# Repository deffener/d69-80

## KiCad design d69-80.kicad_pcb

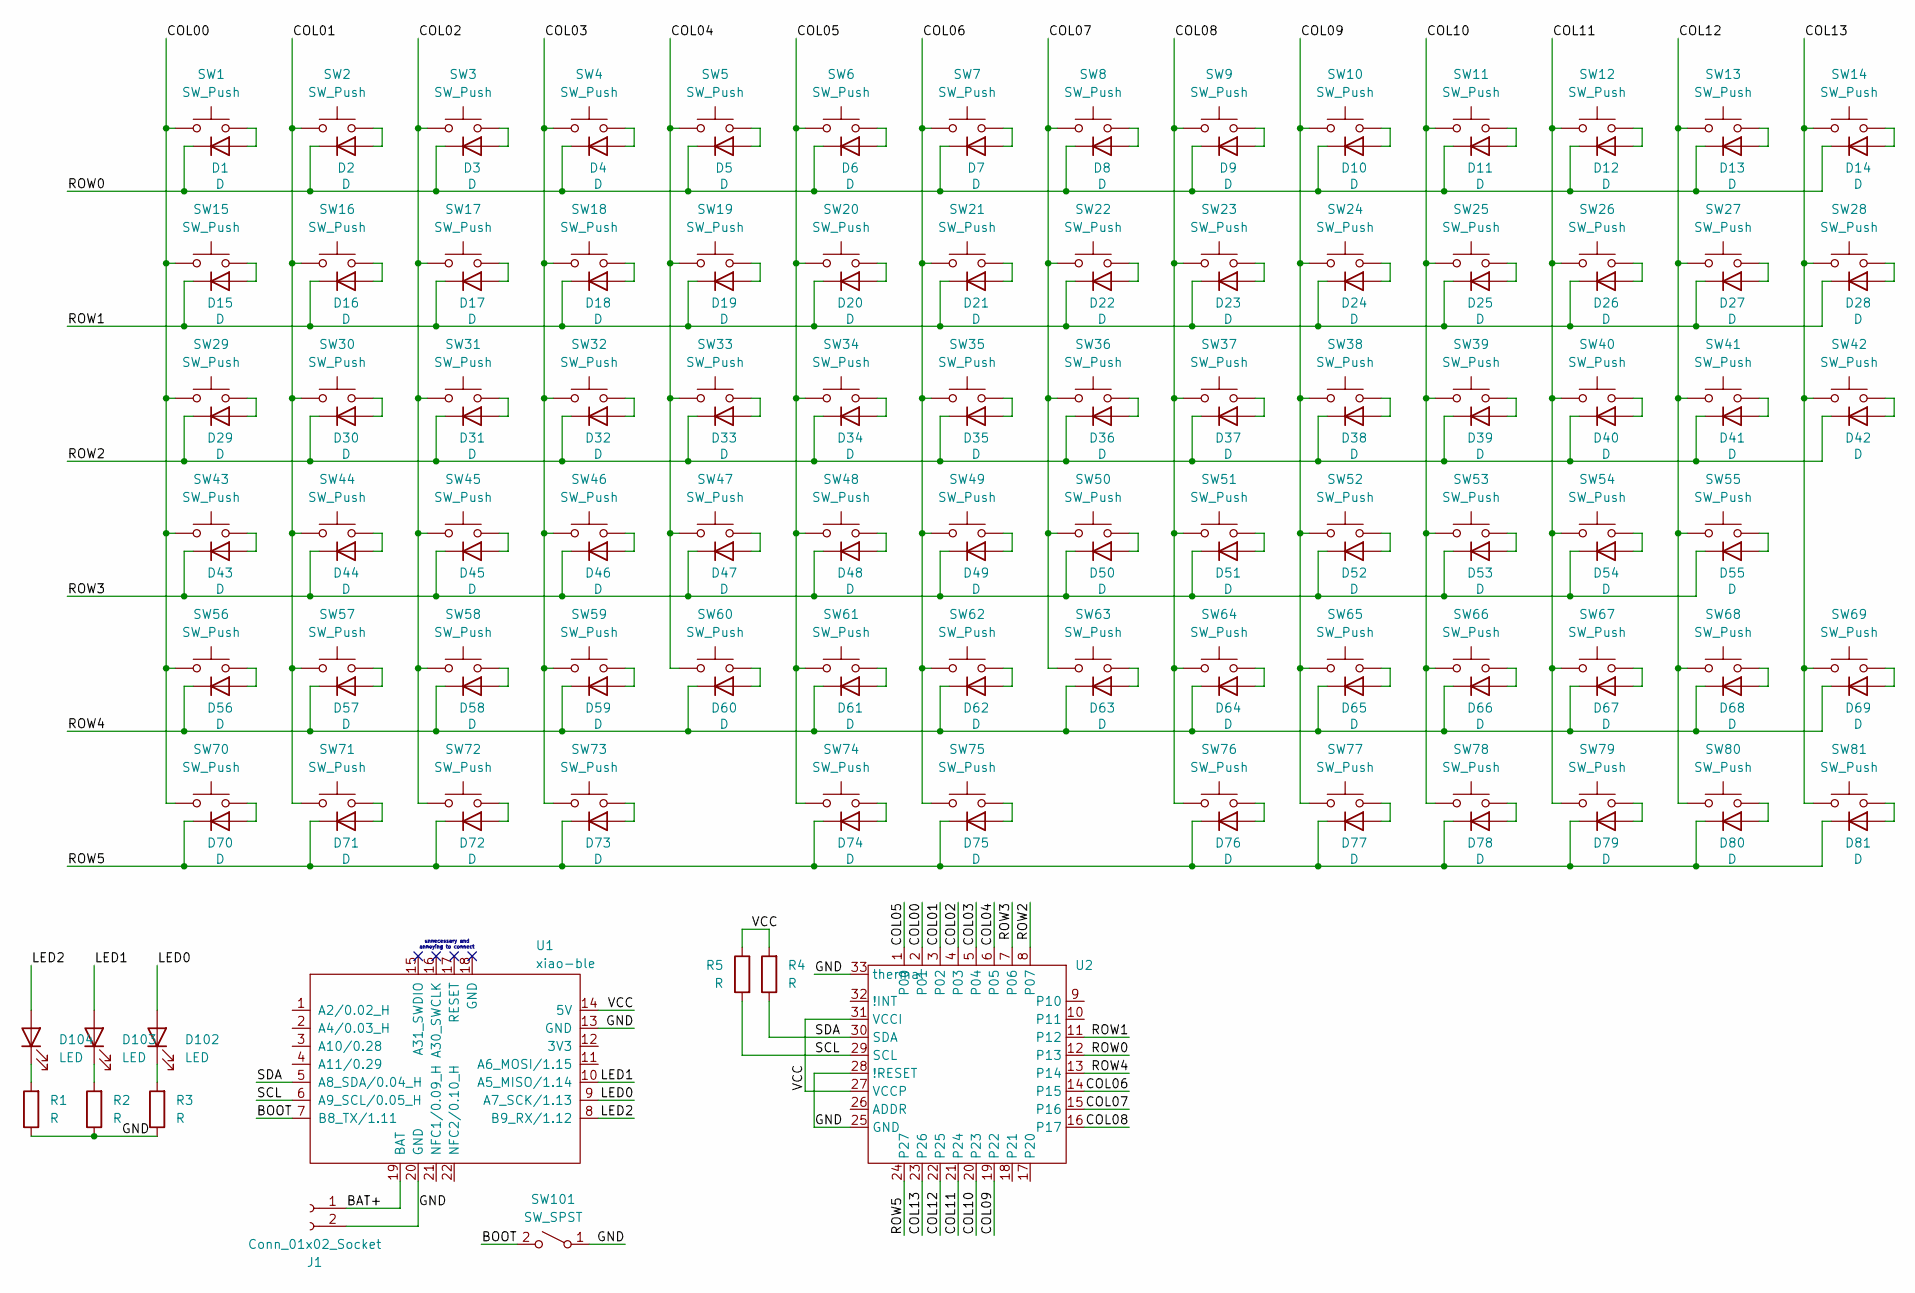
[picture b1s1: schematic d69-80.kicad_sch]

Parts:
D1, D2, D3, D4, D5, D6, D7, D8, D9, D10, D11, D12, D13, D14, D15, D16, D17, D18, D19, D20, D21, D22, D23, D24, D25, D26, D27, D28, D29, D30, D31, D32, D33, D34, D35, D36, D37, D38, D39, D40, D41, D42, D43, D44, D45, D46, D47, D48, D49, D50, D51, D52, D53, D54, D55, D56, D57, D58, D59, D60, D61, D62, D63, D64, D65, D66, D67, D68, D69, D70, D71, D72, D73, D74, D75, D76, D77, D78, D79, D80, D81: D; D_SOD-123
D102, D103, D104: LED; LED_0603_1608Metric_Pad1.05x0.95mm_HandSolder
J1: Conn_01x02_Socket; JST_XH_B2B-XH-AM_1x02_P2.50mm_Vertical
R1, R2, R3, R4, R5: R; R_0603_1608Metric_Pad0.98x0.95mm_HandSolder
SW1, SW15: SW_Push; SW_Hotswap_Kailh_Choc_V1_1.00u_mod3
SW2, SW3, SW4, SW5: SW_Push; SW_Hotswap_Kailh_Choc_V1_1.00u_mod2
SW6, SW7, SW8, SW9, SW10, SW11, SW12, SW13, SW14, SW16, SW17, SW18, SW19, SW20, SW21, SW22, SW23, SW24, SW25, SW26, SW27, SW30, SW31, SW32, SW33, SW34, SW35, SW36, SW37, SW38, SW39, SW40, SW41, SW44, SW45, SW46, SW47, SW48, SW49, SW50, SW51, SW52, SW53, SW54, SW55, SW56, SW57, SW58, SW59, SW60, SW61, SW62, SW63, SW64, SW65, SW66, SW67, SW68, SW70, SW71, SW72, SW73, SW76, SW77, SW78, SW79, SW80, SW81: SW_Push; SW_Hotswap_Kailh_Choc_V1_1.00u_mod1
SW28, SW43, SW69: SW_Push; SW_Hotswap_Kailh_Choc_V1_1.50u_mod1
SW29: SW_Push; SW_Hotswap_Kailh_Choc_V1_1.25u_mod1
SW42: SW_Push; SW_Hotswap_Kailh_Choc_V1_ISOEnter_custom
SW74, SW75: SW_Push; SW_Hotswap_Kailh_Choc_V1_2.00u_mod1
SW101: SW_SPST; combo
U1: xiao-ble; xiao-ble-smd-cutout
U2: QFN-32_EP_5x5_Pitch0.5mm

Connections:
/BAT+: J1.1, U1.19 (BAT)
/BOOT: SW101.2 (B), U1.7 (B8_TX/1.11)
/COL00: SW1.1, SW15.1, SW29.1, SW43.1, SW56.1, SW70.1, U2.2 (P01)
/COL01: SW2.1, SW16.1, SW30.1, SW44.1, SW57.1, SW71.1, U2.3 (P02)
/COL02: SW3.1, SW17.1, SW31.1, SW45.1, SW58.1, SW72.1, U2.4 (P03)
/COL03: SW4.1, SW18.1, SW32.1, SW46.1, SW59.1, SW73.1, U2.5 (P04)
/COL04: SW5.1, SW19.1, SW33.1, SW47.1, SW60.1, U2.6 (P05)
/COL05: SW6.1, SW20.1, SW34.1, SW48.1, SW61.1, SW74.1, U2.1 (P00)
/COL06: SW7.1, SW21.1, SW35.1, SW49.1, SW62.1, SW75.1, U2.14 (P15)
/COL07: SW8.1, SW22.1, SW36.1, SW50.1, SW63.1, U2.15 (P16)
/COL08: SW9.1, SW23.1, SW37.1, SW51.1, SW64.1, SW76.1, U2.16 (P17)
/COL09: SW10.1, SW24.1, SW38.1, SW52.1, SW65.1, SW77.1, U2.19 (P22)
/COL10: SW11.1, SW25.1, SW39.1, SW53.1, SW66.1, SW78.1, U2.20 (P23)
/COL11: SW12.1, SW26.1, SW40.1, SW54.1, SW67.1, SW79.1, U2.21 (P24)
/COL12: SW13.1, SW27.1, SW41.1, SW55.1, SW68.1, SW80.1, U2.22 (P25)
/COL13: SW14.1, SW28.1, SW42.1, SW69.1, SW81.1, U2.23 (P26)
/GND: J1.2, R1.1, R2.1, R3.1, SW101.1 (A), U1.13 (GND), U1.20 (GND), U2.25 (GND), U2.28 (!RESET), U2.33 (thermal)
/LED0: D102.2 (A), U1.9 (A7_SCK/1.13)
/LED1: D103.2 (A), U1.10 (A5_MISO/1.14)
/LED2: D104.2 (A), U1.8 (B9_RX/1.12)
/ROW0: D1.1 (K), D2.1 (K), D3.1 (K), D4.1 (K), D5.1 (K), D6.1 (K), D7.1 (K), D8.1 (K), D9.1 (K), D10.1 (K), D11.1 (K), D12.1 (K), D13.1 (K), D14.1 (K), U2.12 (P13)
/ROW1: D15.1 (K), D16.1 (K), D17.1 (K), D18.1 (K), D19.1 (K), D20.1 (K), D21.1 (K), D22.1 (K), D23.1 (K), D24.1 (K), D25.1 (K), D26.1 (K), D27.1 (K), D28.1 (K), U2.11 (P12)
/ROW2: D29.1 (K), D30.1 (K), D31.1 (K), D32.1 (K), D33.1 (K), D34.1 (K), D35.1 (K), D36.1 (K), D37.1 (K), D38.1 (K), D39.1 (K), D40.1 (K), D41.1 (K), D42.1 (K), U2.8 (P07)
/ROW3: D43.1 (K), D44.1 (K), D45.1 (K), D46.1 (K), D47.1 (K), D48.1 (K), D49.1 (K), D50.1 (K), D51.1 (K), D52.1 (K), D53.1 (K), D54.1 (K), D55.1 (K), U2.7 (P06)
/ROW4: D56.1 (K), D57.1 (K), D58.1 (K), D59.1 (K), D60.1 (K), D61.1 (K), D62.1 (K), D63.1 (K), D64.1 (K), D65.1 (K), D66.1 (K), D67.1 (K), D68.1 (K), D69.1 (K), U2.13 (P14)
/ROW5: D70.1 (K), D71.1 (K), D72.1 (K), D73.1 (K), D74.1 (K), D75.1 (K), D76.1 (K), D77.1 (K), D78.1 (K), D79.1 (K), D80.1 (K), D81.1 (K), U2.24 (P27)
/SCL: R5.2, U1.6 (A9_SCL/0.05_H), U2.29 (SCL)
/SDA: R4.1, U1.5 (A8_SDA/0.04_H), U2.30 (SDA)
/VCC: R4.2, R5.1, U1.14 (5V), U2.27 (VCCP), U2.31 (VCCI)
unnamed: D1.2 (A), SW1.2
unnamed: D2.2 (A), SW2.2
unnamed: D3.2 (A), SW3.2
unnamed: D4.2 (A), SW4.2
unnamed: D5.2 (A), SW5.2
unnamed: D6.2 (A), SW6.2
unnamed: D7.2 (A), SW7.2
unnamed: D8.2 (A), SW8.2
unnamed: D9.2 (A), SW9.2
unnamed: D10.2 (A), SW10.2
unnamed: D11.2 (A), SW11.2
unnamed: D12.2 (A), SW12.2
unnamed: D13.2 (A), SW13.2
unnamed: D14.2 (A), SW14.2
unnamed: D15.2 (A), SW15.2
unnamed: D16.2 (A), SW16.2
unnamed: D17.2 (A), SW17.2
unnamed: D18.2 (A), SW18.2
unnamed: D19.2 (A), SW19.2
unnamed: D20.2 (A), SW20.2
unnamed: D21.2 (A), SW21.2
unnamed: D22.2 (A), SW22.2
unnamed: D23.2 (A), SW23.2
unnamed: D24.2 (A), SW24.2
unnamed: D25.2 (A), SW25.2
unnamed: D26.2 (A), SW26.2
unnamed: D27.2 (A), SW27.2
unnamed: D28.2 (A), SW28.2
unnamed: D29.2 (A), SW29.2
unnamed: D30.2 (A), SW30.2
unnamed: D31.2 (A), SW31.2
unnamed: D32.2 (A), SW32.2
unnamed: D33.2 (A), SW33.2
unnamed: D34.2 (A), SW34.2
unnamed: D35.2 (A), SW35.2
unnamed: D36.2 (A), SW36.2
unnamed: D37.2 (A), SW37.2
unnamed: D38.2 (A), SW38.2
unnamed: D39.2 (A), SW39.2
unnamed: D40.2 (A), SW40.2
unnamed: D41.2 (A), SW41.2
unnamed: D42.2 (A), SW42.2
unnamed: D43.2 (A), SW43.2
unnamed: D44.2 (A), SW44.2
unnamed: D45.2 (A), SW45.2
unnamed: D46.2 (A), SW46.2
unnamed: D47.2 (A), SW47.2
unnamed: D48.2 (A), SW48.2
unnamed: D49.2 (A), SW49.2
unnamed: D50.2 (A), SW50.2
unnamed: D51.2 (A), SW51.2
unnamed: D52.2 (A), SW52.2
unnamed: D53.2 (A), SW53.2
unnamed: D54.2 (A), SW54.2
unnamed: D55.2 (A), SW55.2
unnamed: D56.2 (A), SW56.2
unnamed: D57.2 (A), SW57.2
unnamed: D58.2 (A), SW58.2
unnamed: D59.2 (A), SW59.2
unnamed: D60.2 (A), SW60.2
unnamed: D61.2 (A), SW61.2
unnamed: D62.2 (A), SW62.2
unnamed: D63.2 (A), SW63.2
unnamed: D64.2 (A), SW64.2
unnamed: D65.2 (A), SW65.2
unnamed: D66.2 (A), SW66.2
unnamed: D67.2 (A), SW67.2
unnamed: D68.2 (A), SW68.2
unnamed: D69.2 (A), SW69.2
unnamed: D70.2 (A), SW70.2
unnamed: D71.2 (A), SW71.2
unnamed: D72.2 (A), SW72.2
unnamed: D73.2 (A), SW73.2
unnamed: D74.2 (A), SW74.2
unnamed: D75.2 (A), SW75.2
unnamed: D76.2 (A), SW76.2
unnamed: D77.2 (A), SW77.2
unnamed: D78.2 (A), SW78.2
unnamed: D79.2 (A), SW79.2
unnamed: D80.2 (A), SW80.2
unnamed: D81.2 (A), SW81.2
unnamed: D102.1 (K), R3.2
unnamed: D103.1 (K), R2.2
unnamed: D104.1 (K), R1.2

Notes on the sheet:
unnecessary and annoying to connect

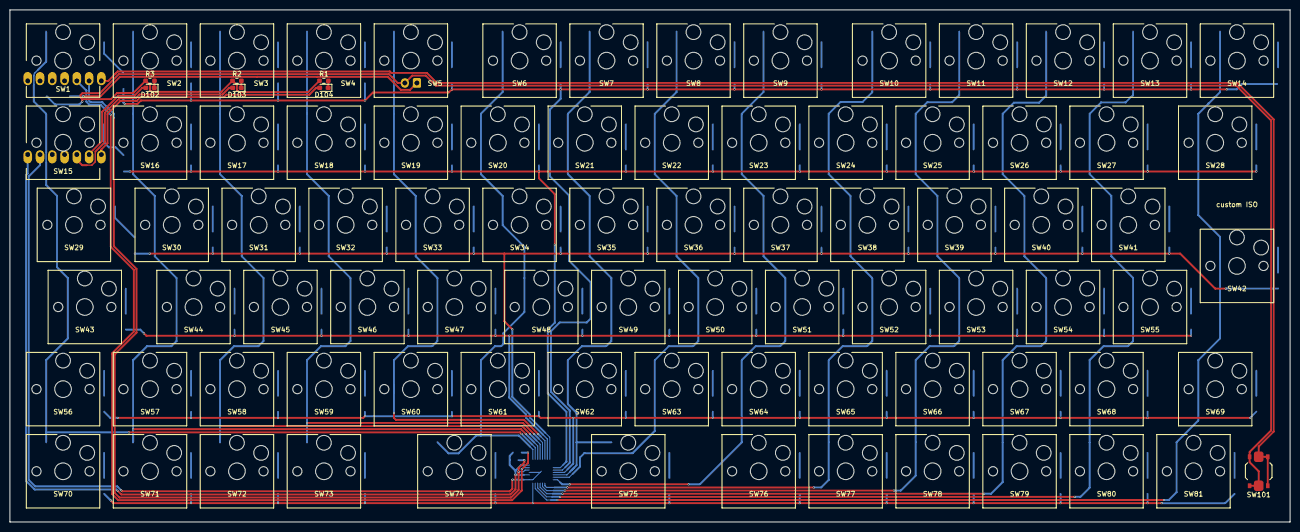
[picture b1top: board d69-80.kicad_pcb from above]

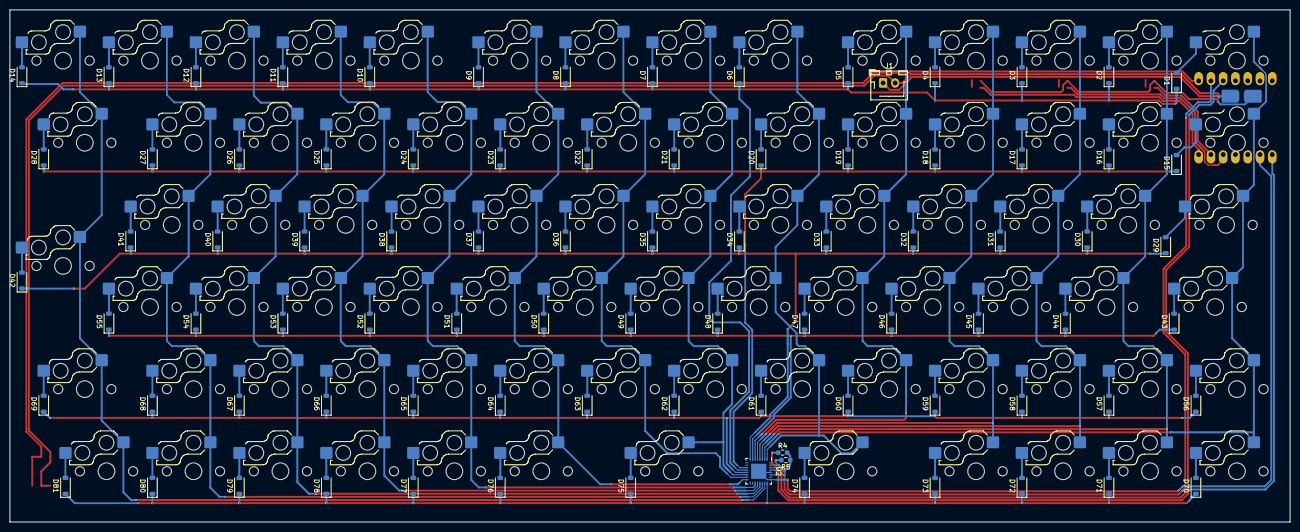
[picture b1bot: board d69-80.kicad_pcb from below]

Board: 2 copper layers, 265.0 x 106.0 mm, 174 parts (86 on the bottom side), 113 nets.

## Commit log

2024-11-26 first push
2024-11-26 remove random crap
2024-11-26 add layout image
2024-11-27 adds mcu and io-expander, initial wiring
2024-12-20 adds leds, connects switch and some cleanup
2024-12-22 more cleanup
2025-01-12 even more cleanup.. still wip
2025-02-21 Add I2C pullups (oops), switch to wakeup switch from battery cutoff
2025-02-24 drc rules and cleanup
